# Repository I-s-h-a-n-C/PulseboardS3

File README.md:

# Pulseboard S3
This is an ESP32 S3 based Devboard, designed to be used in conjunction with EMGs and EKGs. As with all ESP32S3 Devboards, it has WiFi and Bluetooth capibilities.

## Features
* ESP32 S3 Microcontroller
* Wifi and Bluetooth
* Onboard Battery Charging
* Onboard temperature and moisture sensor
* 38 GPIO pins
* 3.3 and 5v
* USB-C Connectivity (Impedence matched)
* Status LEDS
* 4-layer PCB design

## PCB
### Schematic

### Layer 1 - Routing, Layer 2 - GND, Layer 3 - GND (mostly), Layer 4 - Routing

### Front

### Back

### Order

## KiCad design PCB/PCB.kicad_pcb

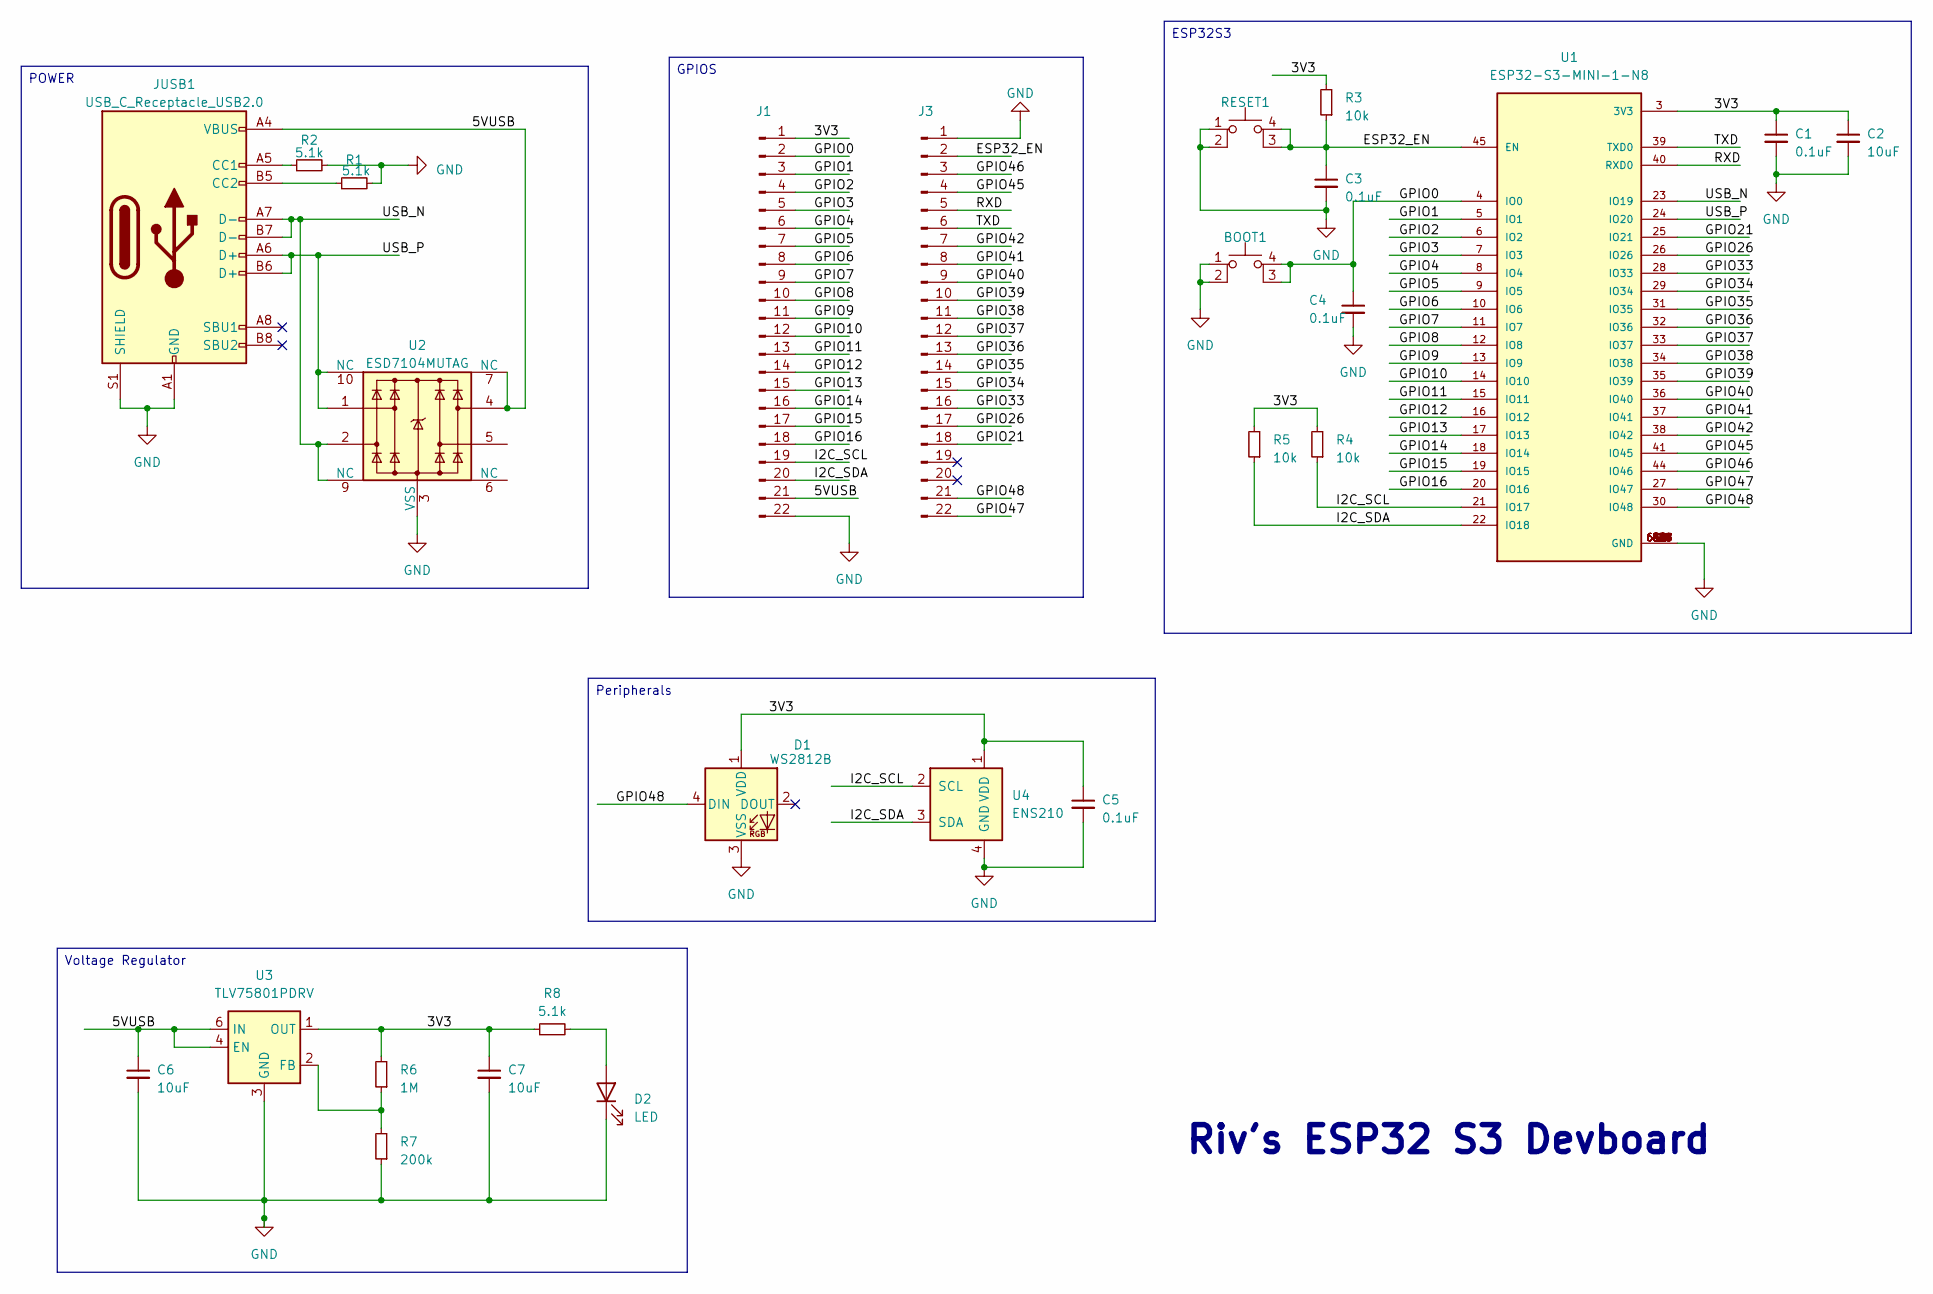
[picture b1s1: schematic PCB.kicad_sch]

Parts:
BOOT1: SW_SPST_PTS810
C1, C3, C4, C5: 0.1uF; C_0603_1608Metric
C2, C6, C7: 10uF; C_0603_1608Metric
D1: WS2812B; LED_WS2812B_PLCC4_5.0x5.0mm_P3.2mm
D2: LED; LED_0603_1608Metric
J1, J3: PinHeader_1x22_P2.54mm_Vertical
JUSB1: USB_C_Receptacle_USB2.0; USB_C_Receptacle_GCT_USB4105-xx-A_16P_TopMnt_Horizontal
R1, R2, R8: 5.1k; R_0603_1608Metric
R3, R4, R5: 10k; R_0603_1608Metric
R6: 1M; R_0603_1608Metric
R7: 200k; R_0603_1608Metric
RESET1: SW_SPST_PTS810
U1: ESP32-S3-MINI-1-N8; XCVR_ESP32-S3-MINI-1-N8; PARTREV v0.6
U2: ESD7104MUTAG; Diodes_UDFN-10_1.0x2.5mm_P0.5mm
U3: TLV75801PDRV; WSON-6-1EP_2x2mm_P0.65mm_EP1x1.6mm
U4: ENS210; AMS_QFN-4-1EP_2x2mm_P0.95mm_EP0.7x1.6mm

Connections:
/3V3: C1.1, C2.1, C5.1, C7.1, D1.1 (VDD), J1.1, R3.2, R4.2, R5.2, R6.2, R8.1, U1.3 (3V3), U3.1 (OUT), U4.1 (VDD)
/5VUSB: C6.1, J1.21, JUSB1.A4 (VBUS), JUSB1.A9 (VBUS), JUSB1.B4 (VBUS), JUSB1.B9 (VBUS), U2.4, U2.7 (NC), U3.4 (EN), U3.6 (IN)
/ESP32_EN: C3.1, J3.2, R3.1, RESET1.3 (K), RESET1.4 (A), U1.45 (EN)
/GPIO0: BOOT1.3 (K), BOOT1.4 (A), C4.1, J1.2, U1.4 (IO0)
/GPIO1: J1.3, U1.5 (IO1)
/GPIO2: J1.4, U1.6 (IO2)
/GPIO3: J1.5, U1.7 (IO3)
/GPIO4: J1.6, U1.8 (IO4)
/GPIO5: J1.7, U1.9 (IO5)
/GPIO6: J1.8, U1.10 (IO6)
/GPIO7: J1.9, U1.11 (IO7)
/GPIO8: J1.10, U1.12 (IO8)
/GPIO9: J1.11, U1.13 (IO9)
/GPIO10: J1.12, U1.14 (IO10)
/GPIO11: J1.13, U1.15 (IO11)
/GPIO12: J1.14, U1.16 (IO12)
/GPIO13: J1.15, U1.17 (IO13)
/GPIO14: J1.16, U1.18 (IO14)
/GPIO15: J1.17, U1.19 (IO15)
/GPIO16: J1.18, U1.20 (IO16)
/GPIO21: J3.18, U1.25 (IO21)
/GPIO26: J3.17, U1.26 (IO26)
/GPIO33: J3.16, U1.28 (IO33)
/GPIO34: J3.15, U1.29 (IO34)
/GPIO35: J3.14, U1.31 (IO35)
/GPIO36: J3.13, U1.32 (IO36)
/GPIO37: J3.12, U1.33 (IO37)
/GPIO38: J3.11, U1.34 (IO38)
/GPIO39: J3.10, U1.35 (IO39)
/GPIO40: J3.9, U1.36 (IO40)
/GPIO41: J3.8, U1.37 (IO41)
/GPIO42: J3.7, U1.38 (IO42)
/GPIO45: J3.4, U1.41 (IO45)
/GPIO46: J3.3, U1.44 (IO46)
/GPIO47: J3.22, U1.27 (IO47)
/GPIO48: D1.4 (DIN), J3.21, U1.30 (IO48)
/I2C_SCL: J1.19, R4.1, U1.21 (IO17), U4.2 (SCL)
/I2C_SDA: J1.20, R5.1, U1.22 (IO18), U4.3 (SDA)
/RXD: J3.5, U1.40 (RXD0)
/TXD: J3.6, U1.39 (TXD0)
/USB_N: JUSB1.A7 (D-), JUSB1.B7 (D-), U1.23 (IO19), U2.2, U2.9 (NC)
/USB_P: JUSB1.A6 (D+), JUSB1.B6 (D+), U1.24 (IO20), U2.1, U2.10 (NC)
GND: BOOT1.1, BOOT1.2, C1.2, C2.2, C3.2, C4.2, C5.2, C6.2, C7.2, D1.3 (VSS), D2.1 (K), J1.22, J3.1, JUSB1.A1 (GND), JUSB1.A12 (GND), JUSB1.B1 (GND), JUSB1.B12 (GND), JUSB1.S1 (SHIELD), R1.2, R2.2, R7.1, RESET1.1, RESET1.2, U1.1 (GND), U1.2 (GND), U1.42 (GND), U1.43 (GND), U1.46 (GND), U1.47 (GND), U1.48 (GND), U1.49 (GND), U1.50 (GND), U1.51 (GND), U1.52 (GND), U1.53 (GND), U1.54 (GND), U1.55 (GND), U1.56 (GND), U1.57 (GND), U1.58 (GND), U1.59 (GND), U1.60 (GND), U1.61 (GND), U1.61_1 (GND), U1.61_2 (GND), U1.61_3 (GND), U1.61_4 (GND), U1.61_5 (GND), U1.61_6 (GND), U1.61_7 (GND), U1.61_8 (GND), U1.62 (GND), U1.63 (GND), U1.64 (GND), U1.65 (GND), U2.3 (VSS), U2.8 (VSS), U3.3 (GND), U3.7 (GND), U4.4 (GND), U4.5 (GND)
unnamed: D2.2 (A), R8.2
unnamed: JUSB1.A5 (CC1), R2.1
unnamed: JUSB1.B5 (CC2), R1.1
unnamed: R6.1, R7.2, U3.2 (FB)

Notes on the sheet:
Riv's ESP32 S3 Devboard
Peripherals
POWER
Voltage Regulator
ESP32S3
GPIOS

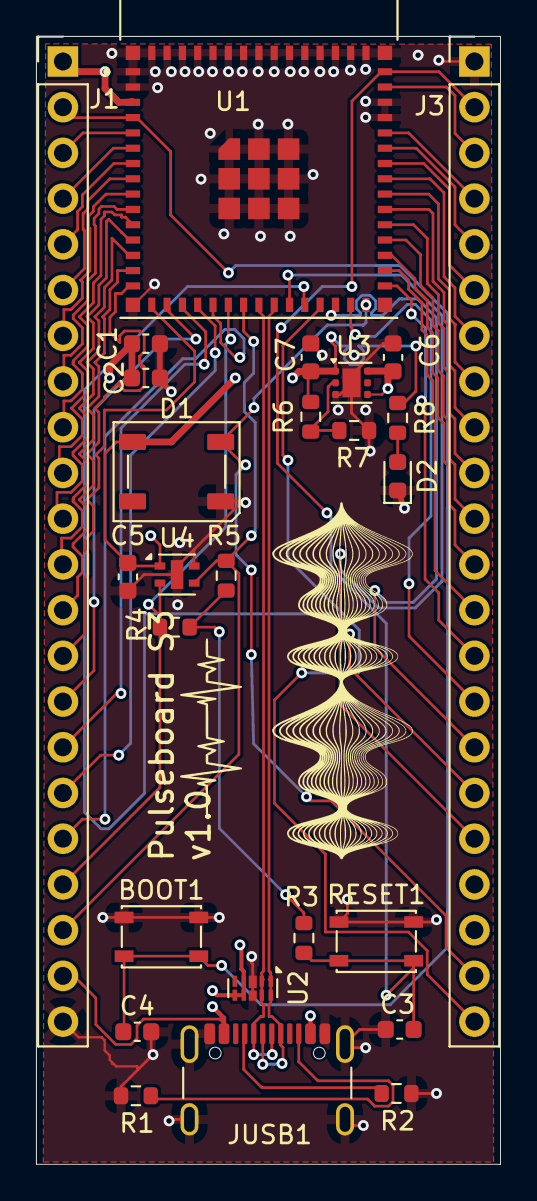
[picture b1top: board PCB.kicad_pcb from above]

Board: 4 copper layers, 25.8 x 62.7 mm, 26 parts (0 on the bottom side), 47 nets.

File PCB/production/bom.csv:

Designator,Footprint,Quantity,Value,LCSC Part #
"BOOT1, RESET1",SW_SPST_PTS810,2,~,
"C1, C3, C4, C5",0603,4,0.1uF,
"C2, C6, C7",0603,3,10uF,
D1,LED_WS2812B_PLCC4_5.0x5.0mm_P3.2mm,1,WS2812B,
D2,0603,1,LED,
"J1, J3",PinHeader_1x22_P2.54mm_Vertical,2,~,
JUSB1,USB_C_Receptacle_GCT_USB4105-xx-A_16P_TopMnt_Horizontal,1,USB_C_Receptacle_USB2.0,
"R1, R2, R8",0603,3,5.1k,
"R3, R4, R5",0603,3,10k,
R6,0603,1,1M,
R7,0603,1,200k,
U1,XCVR_ESP32-S3-MINI-1-N8,1,ESP32-S3-MINI-1-N8,
U2,Diodes_UDFN-10_1.0x2.5mm_P0.5mm,1,ESD7104MUTAG,
U3,WSON-6-1EP_2x2mm_P0.65mm_EP1x1.6mm,1,TLV75801PDRV,
U4,AMS_QFN-4-1EP_2x2mm_P0.95mm_EP0.7x1.6mm,1,ENS210,

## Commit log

2025-12-14 added the files for the board
2025-12-14 done
2025-12-14 fixed mistake on impdence
2025-12-15 added all needed files
2025-12-15 fixed some stuff
2025-12-15 Update README with features and PCB details
    Added detailed features and PCB information with images.
